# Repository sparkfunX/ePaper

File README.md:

SparkFun 3 Color ePaper Displays
===========================================================

[*SparkX 3 Color ePaper Display - 1.54" (SPX-14892)*](https://www.sparkfun.com/products/14892)

Repository Contents
-------------------

* **/1.54in display** - Datasheets and board files for the 1.54" display
* **/4.2in display** - Datasheets for the 4.2" display
* **/7.5in display** - Datasheets for the 7.5" display
* **ePaper.lbr** - Eagle library for ePaper board components

License Information
-------------------

This product is _**open source**_! 

Please use, reuse, and modify these files as you see fit. Please maintain attribution to SparkFun Electronics and release anything derivative under the same license.

Distributed as-is; no warranty is given.

- Your friends at SparkFun.

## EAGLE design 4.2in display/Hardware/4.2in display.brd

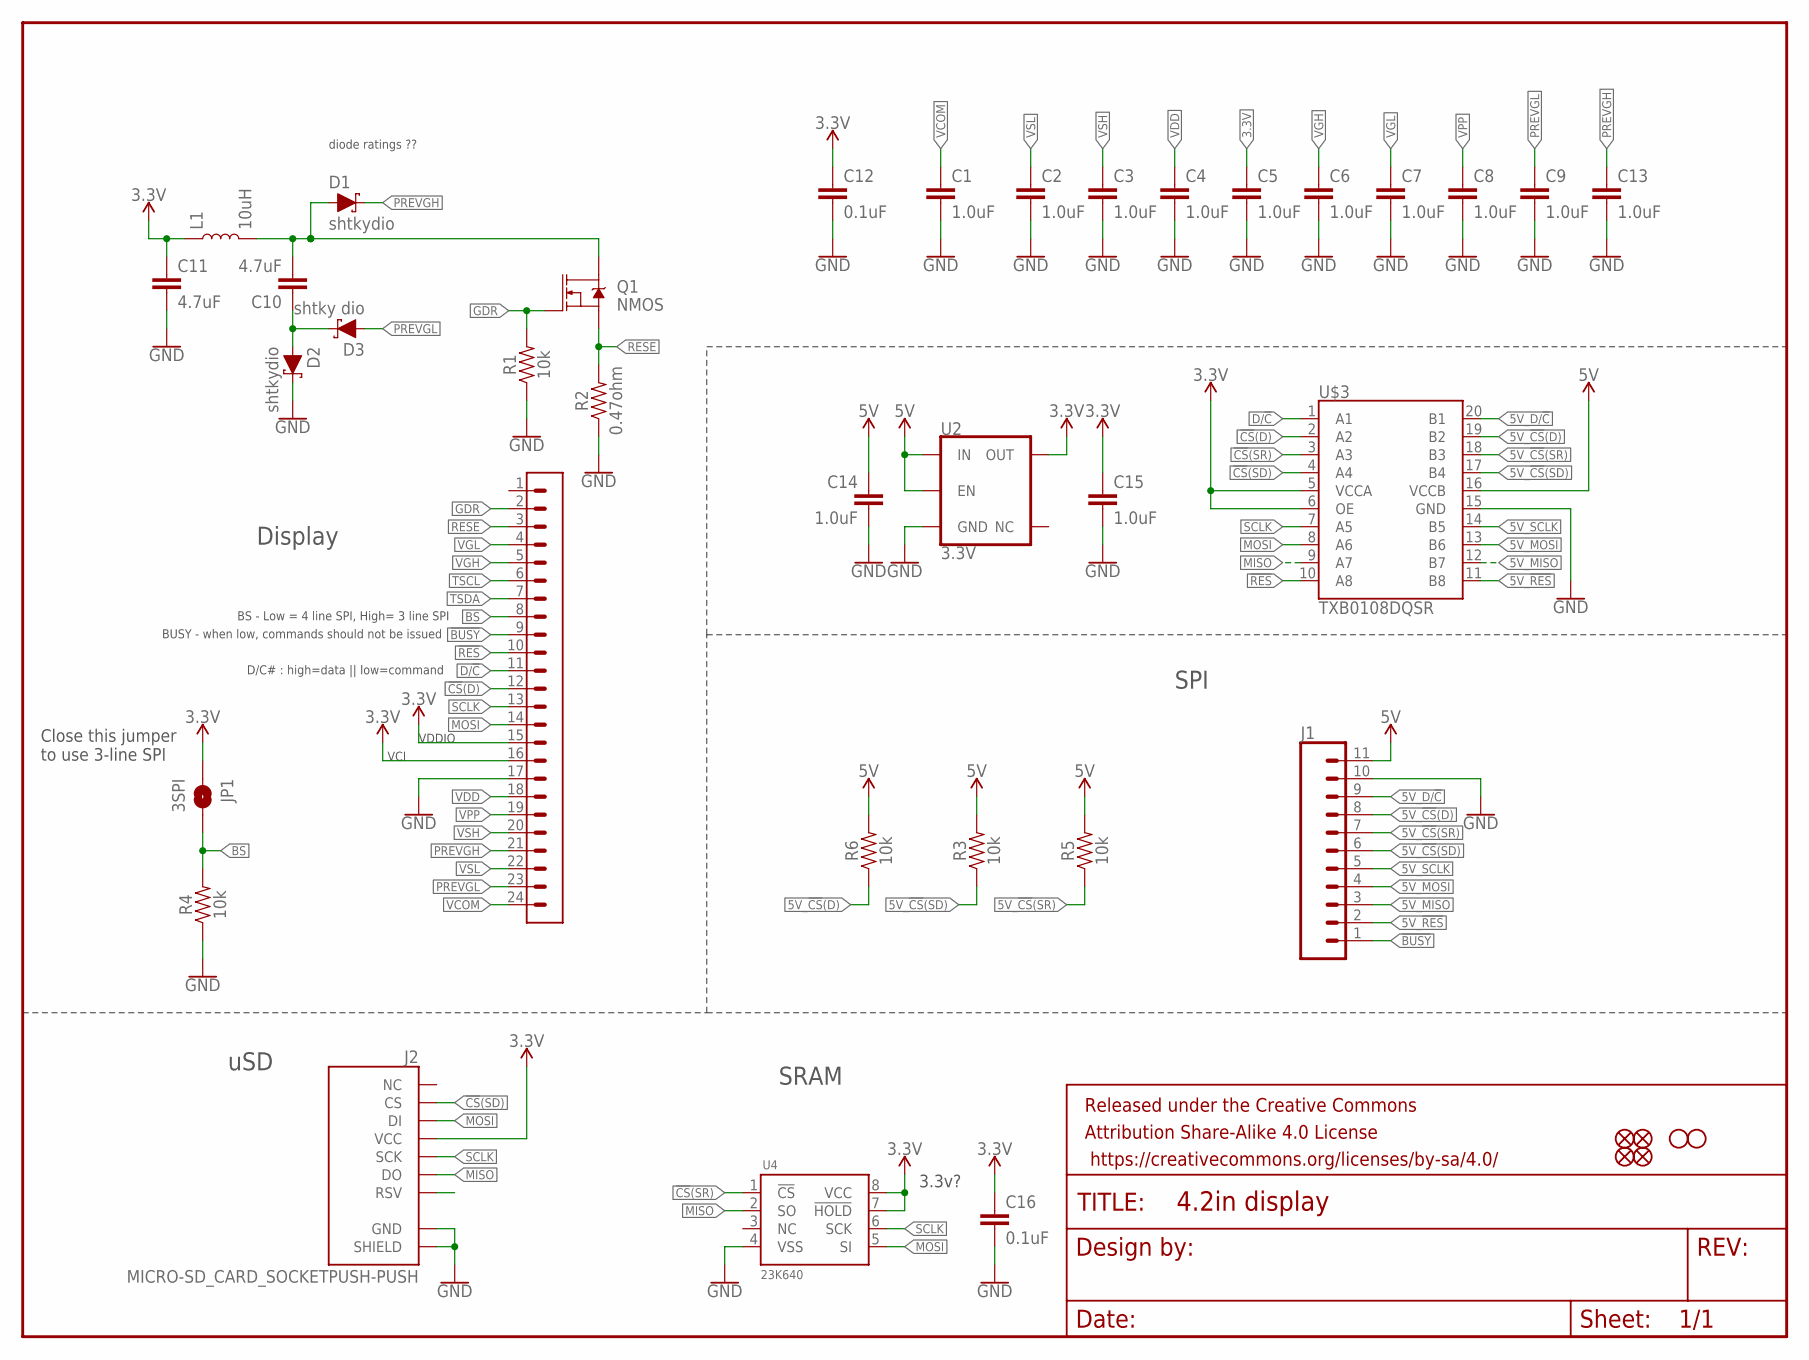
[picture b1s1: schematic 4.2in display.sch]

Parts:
C1, C14, C15: 1.0uF; 0603
C2, C3, C4, C5, C6, C7, C8, C9, C13: 1.0uF; 0805
C10, C11: 4.7uF; 0805
C12, C16: 0.1uF; 0603
D1, D2: shtkydio; SOD-323
D3: shtky dio; SOD-323
FD1, FD2, FD3, FD4: FIDUCIALUFIDUCIAL; FIDUCIAL-MICRO
FRAME1: FRAME-LETTER; CREATIVE_COMMONS
H1, H2: STAND-OFF
J1: CONN_111X11_NO_SILK; 1X11_NO_SILK
J2: MICRO-SD_CARD_SOCKETPUSH-PUSH; MICRO-SD-SOCKET
JP1: 3SPI; SMT-JUMPER_2_NO_SILK
L1: 10uH; INDUCTOR_4.7UH
Q1: NMOS; SOT323
R1, R3, R4, R5, R6: 10k; 0603
R2: 0.47ohm; 0603
U2: 3.3V; SOT23-5
U4: 23K640; SO08
U$1: 24_PIN_FPC_0.5MM
U$3: TXB0108DQSR; UFDFN-20

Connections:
3.3V: C5.1, C11.1, C12.1, C15.1, C16.1, J2.VCC, JP1.1, L1.P$1 (1), U2.5 (OUT), U4.7 (!HOLD), U4.8 (VCC), U$1.15, U$1.16, U$3.5 (VCCA), U$3.6 (OE)
5V: C14.1, J1.11, R3.2, R5.2, R6.2, U2.1 (IN), U2.3 (EN), U$3.16 (VCCB)
5V_!CS!(D): J1.8, R6.1, U$3.19 (B2)
5V_!CS!(SD): J1.6, R3.1, U$3.17 (B4)
5V_!CS!(SR): J1.7, R5.1, U$3.18 (B3)
5V_!RES: J1.2, U$3.11 (B8)
5V_D/!C: J1.9, U$3.20 (B1)
5V_MISO: J1.3, U$3.12 (B7)
5V_MOSI: J1.4, U$3.13 (B6)
5V_SCLK: J1.5, U$3.14 (B5)
!BUSY: J1.1, U$1.9
!CS!(D): U$1.12, U$3.2 (A2)
!CS!(SD): J2.CS, U$3.4 (A4)
!CS!(SR): U4.1 (!CS), U$3.3 (A3)
!RES: U$1.10, U$3.10 (A8)
BS: JP1.2, R4.2, U$1.8
D/!C: U$1.11, U$3.1 (A1)
GDR: Q1.1 (G), R1.2, U$1.2
GND: C1.2, C2.2, C3.2, C4.2, C5.2, C6.2, C7.2, C8.2, C9.2, C11.2, C12.2, C13.2, C14.2, C15.2, C16.2, D2.C, J1.10, J2.CD1 (SHIELD), J2.GND, R1.1, R2.1, R4.1, U2.2 (GND), U4.4 (VSS), U$1.17, U$3.15 (GND)
MISO: J2.DO, U4.2 (SO), U$3.9 (A7)
MOSI: J2.DI, U4.5 (SI), U$1.14, U$3.8 (A6)
unnamed: C10.1, D2.A, D3.C
unnamed: C10.2, D1.A, L1.P$2 (2), Q1.3 (D)
PREVGH: C13.1, D1.C, U$1.21
PREVGL: C9.1, D3.A, U$1.23
RESE: Q1.2 (S), R2.2, U$1.3
SCLK: J2.SCLK (SCK), U4.6 (SCK), U$1.13, U$3.7 (A5)
TSCL: U$1.6
TSDA: U$1.7
VCOM: C1.1, U$1.24
VDD: C4.1, U$1.18
VGH: C6.1, U$1.5
VGL: C7.1, U$1.4
VPP: C8.1, U$1.19
VSH: C3.1, U$1.20
VSL: C2.1, U$1.22

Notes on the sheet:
D/C# : high=data || low=command
BUSY - when low, commands should not be issued
BS - Low = 4 line SPI, High= 3 line SPI
diode ratings ??
VDDIO
VCI
Display
SPI
uSD
3.3v?
Close this jumper to use 3-line SPI
SRAM

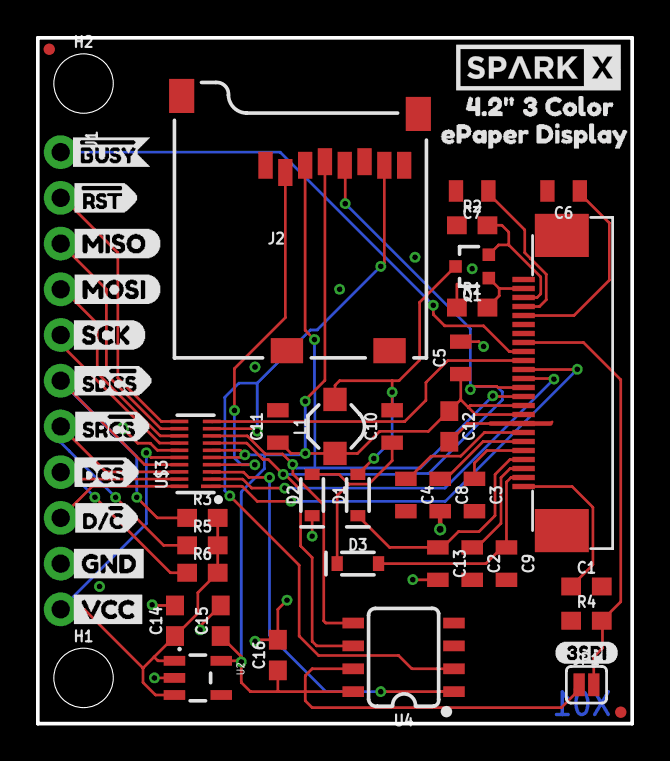
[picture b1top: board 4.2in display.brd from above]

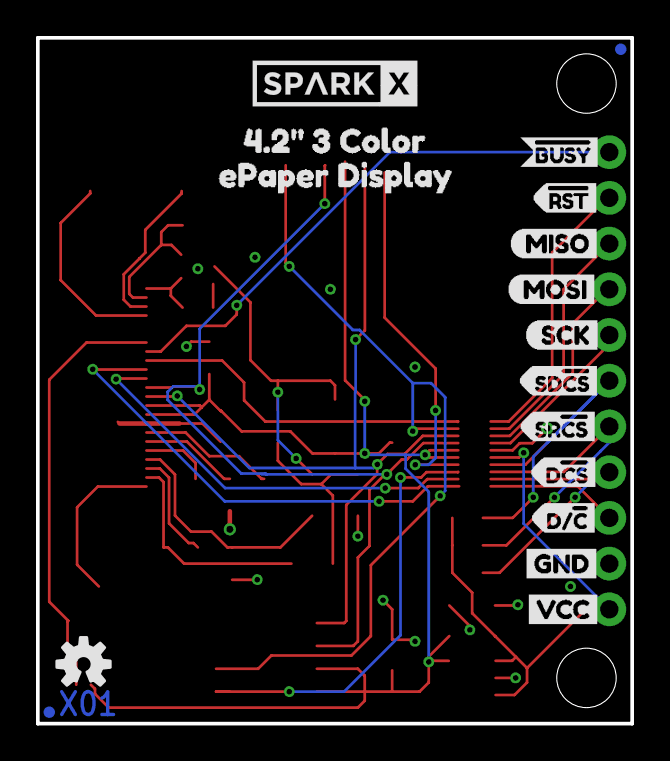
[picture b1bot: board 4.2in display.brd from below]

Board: 2 copper layers, 33.0 x 38.1 mm, 73 parts (18 on the bottom side), 34 nets.

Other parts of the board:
U$2: OSHW-LOGO-S
U$4: #BUSY0
U$5, U$18: SPARKX-LOGO4; SPARKX-MEDIUM
U$6: #BUSY1
U$7: D##C10
U$8: MISO1
U$9: D#CS2
U$10: SD#CS0
U$11: #RST1
U$12: 3SPI0
U$13, U$21: VCC9
U$14: GND9
U$15: SR#CS1
U$16: MOSI0
U$17: SCK2
U$19: 3_COLOR2
U$20: #RST2
U$22: 3_COLOR3
U$23: 4#2#0
U$24: MISO3
U$25: MOSI4
U$26: SCK5
U$27: SD#CS6
U$28: SR#CS7
U$29: D#CS8
U$30: D##C9
U$31: GND11
U$32: EPAPER_DISPLAY5
U$33: EPAPER_DISPLAY4
U$34: 4#2#1

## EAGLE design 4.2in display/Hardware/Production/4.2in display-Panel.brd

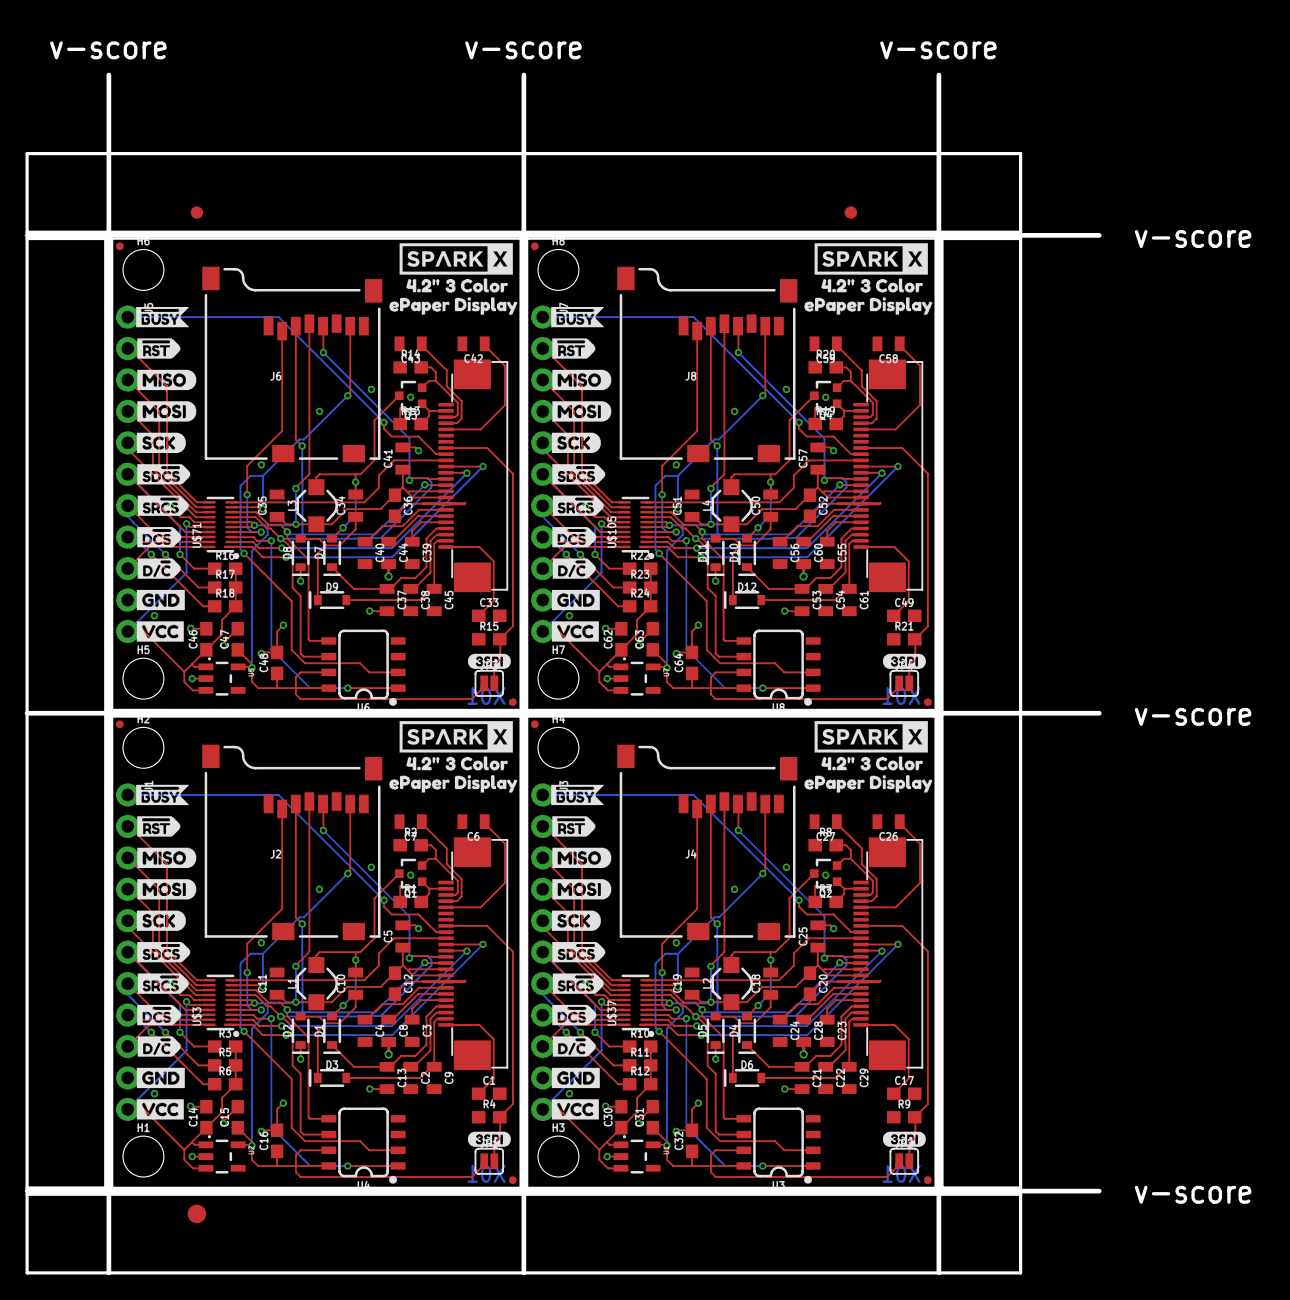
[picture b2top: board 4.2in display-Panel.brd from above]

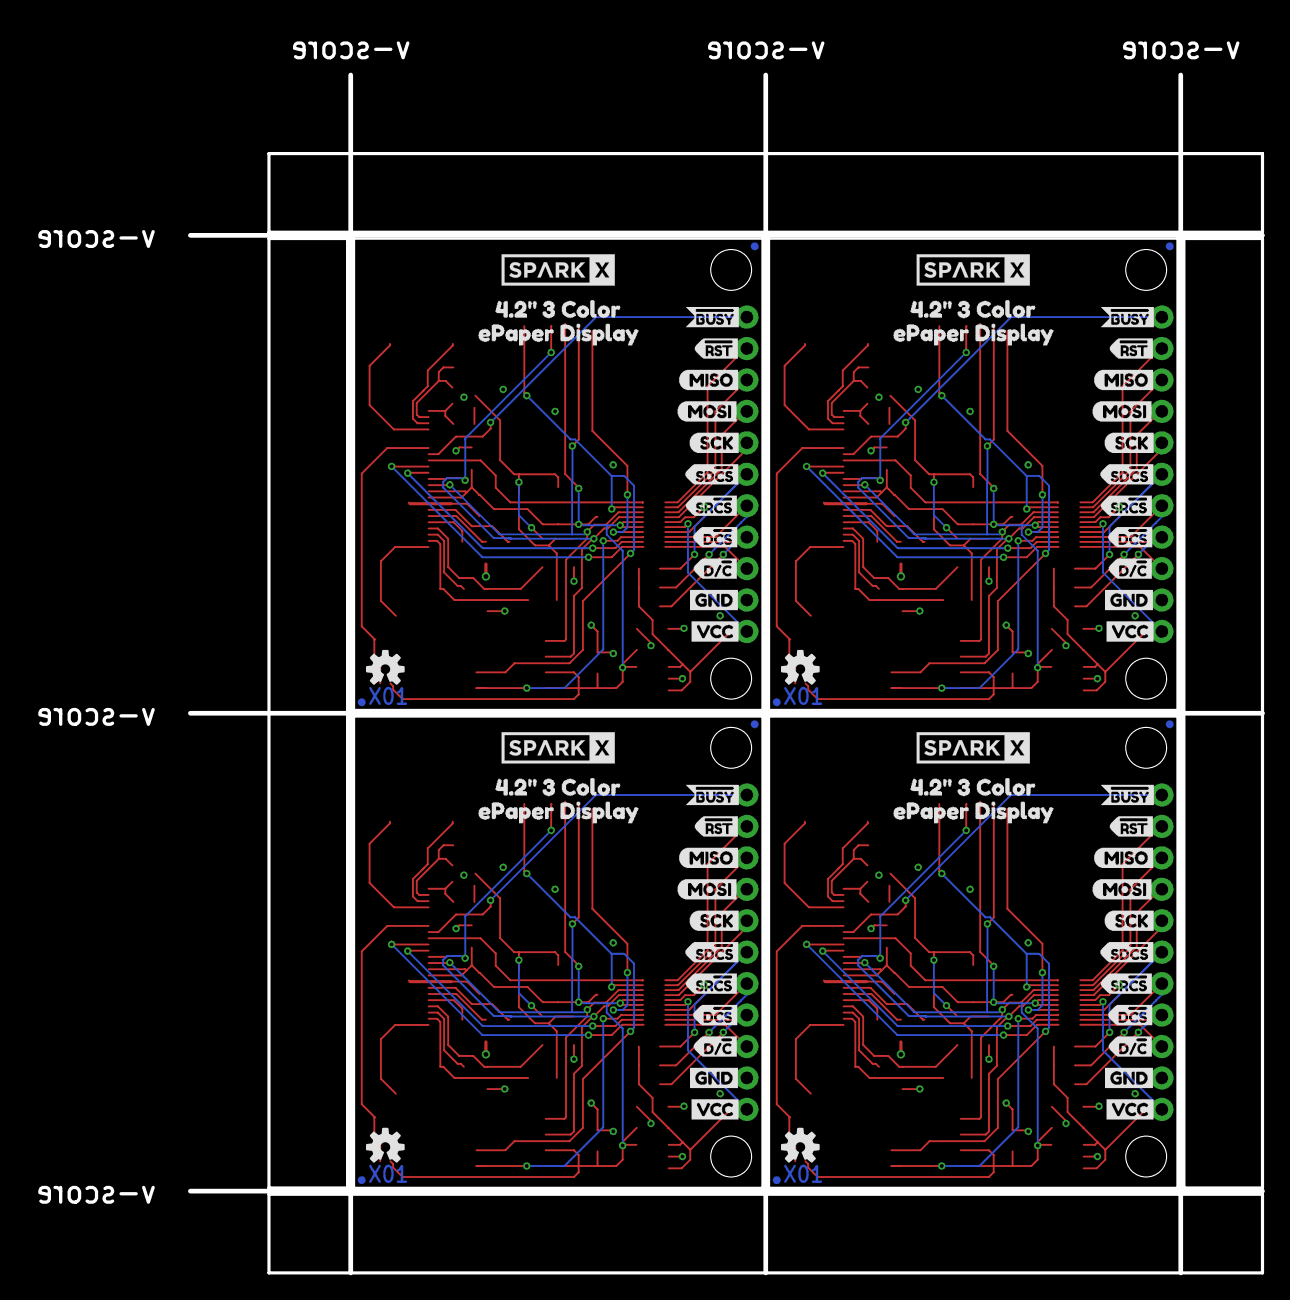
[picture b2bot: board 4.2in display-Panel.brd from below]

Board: 2 copper layers, 99.8 x 100.6 mm, 291 parts (72 on the bottom side), 136 nets.

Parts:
C1, C14, C15, C17, C30, C31, C33, C46, C47, C49, C62, C63: 1.0uF; 0603
C2, C3, C4, C5, C6, C7, C8, C9, C13, C21, C22, C23, C24, C25, C26, C27, C28, C29, C37, C38, C39, C40, C41, C42, C43, C44, C45, C53, C54, C55, C56, C57, C58, C59, C60, C61: 1.0uF; 0805
C10, C11, C18, C19, C34, C35, C50, C51: 4.7uF; 0805
C12, C16, C20, C32, C36, C48, C52, C64: 0.1uF; 0603
D1, D2, D3, D4, D5, D6, D7, D8, D9, D10, D11, D12: 0.5A/40V/420mV; SOD-323
E$1, E$2: FIDUCIAL-1X2
E$3: FIDUCIAL-1.5X3
FD1, FD2, FD3, FD4, FD5, FD6, FD7, FD8, FD9, FD10, FD11, FD12, FD13, FD14, FD15, FD16: FIDUCIALUFIDUCIAL; FIDUCIAL-MICRO
H1, H2, H3, H4, H5, H6, H7, H8: STAND-OFF
J1, J3, J5, J7: 1X11_NO_SILK
J2, J4, J6, J8: MICRO-SD_CARD_SOCKETPUSH-PUSH; MICRO-SD-SOCKET
JP1, JP2, JP3, JP4: 3SPI; SMT-JUMPER_2_NO_SILK
L1, L2, L3, L4: 10uH; INDUCTOR_4.7UH
Q1, Q2, Q3, Q4: 310mA/60V/1.6Ω; SOT323
R1, R3, R4, R5, R6, R7, R9, R10, R11, R12, R13, R15, R16, R17, R18, R19, R21, R22, R23, R24: 10k; 0603
R2, R8, R14, R20: 0.47ohm; 0603
U1, U2, U5, U7: 3.3V; SOT23-5
U3, U4, U6, U8: 23K640; SO08
U$1, U$35, U$69, U$103: 24_PIN_FPC_0.5MM
U$2, U$36, U$70, U$104: OSHW-LOGO-S
U$3, U$37, U$71, U$105: TXB0108DQSR; UFDFN-20
U$4, U$47, U$81, U$115: #BUSY0
U$5, U$18, U$48, U$62, U$82, U$96, U$116, U$130: SPARKX-LOGO4; SPARKX-MEDIUM
U$6, U$49, U$83, U$117: #BUSY1
U$7, U$38, U$72, U$106: D##C10
U$8, U$44, U$78, U$112: MISO1
U$9, U$41, U$75, U$109: D#CS2
U$10, U$42, U$76, U$110: SD#CS0
U$11, U$39, U$73, U$107: #RST1
U$12, U$59, U$93, U$127: 3SPI0
U$13, U$21, U$60, U$61, U$94, U$95, U$128, U$129: VCC9
U$14, U$40, U$74, U$108: GND9
U$15, U$43, U$77, U$111: SR#CS1
U$16, U$45, U$79, U$113: MOSI0
U$17, U$46, U$80, U$114: SCK2
U$19, U$63, U$97, U$131: 3_COLOR2
U$20, U$50, U$84, U$118: #RST2
U$22, U$64, U$98, U$132: 3_COLOR3
U$23, U$65, U$99, U$133: 4#2#0
U$24, U$51, U$85, U$119: MISO3
U$25, U$52, U$86, U$120: MOSI4
U$26, U$53, U$87, U$121: SCK5
U$27, U$54, U$88, U$122: SD#CS6
U$28, U$55, U$89, U$123: SR#CS7
U$29, U$56, U$90, U$124: D#CS8
U$30, U$57, U$91, U$125: D##C9
U$31, U$58, U$92, U$126: GND11
U$32, U$67, U$101, U$135: EPAPER_DISPLAY5
U$33, U$66, U$100, U$134: EPAPER_DISPLAY4
U$34, U$68, U$102, U$136: 4#2#1

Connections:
3.3V: C5.1, C11.1, C12.1, C15.1, C16.1, J2.VCC, JP1.1, L1.P$1, U2.5, U4.7, U4.8, U$1.15, U$1.16, U$3.5, U$3.6
3.3V1: C19.1, C20.1, C25.1, C31.1, C32.1, J4.VCC, JP2.1, L2.P$1, U1.5, U3.7, U3.8, U$35.15, U$35.16, U$37.5, U$37.6
3.3V2: C35.1, C36.1, C41.1, C47.1, C48.1, J6.VCC, JP3.1, L3.P$1, U5.5, U6.7, U6.8, U$69.15, U$69.16, U$71.5, U$71.6
3.3V3: C51.1, C52.1, C57.1, C63.1, C64.1, J8.VCC, JP4.1, L4.P$1, U7.5, U8.7, U8.8, U$103.15, U$103.16, U$105.5, U$105.6
5V: C14.1, J1.11, R3.2, R5.2, R6.2, U2.1, U2.3, U$3.16
5V1: C30.1, J3.11, R10.2, R11.2, R12.2, U1.1, U1.3, U$37.16
5V2: C46.1, J5.11, R16.2, R17.2, R18.2, U5.1, U5.3, U$71.16
5V3: C62.1, J7.11, R22.2, R23.2, R24.2, U7.1, U7.3, U$105.16
5V_!CS!(D): J1.8, R6.1, U$3.19
5V_!CS!(D)1: J3.8, R12.1, U$37.19
5V_!CS!(D)2: J5.8, R18.1, U$71.19
5V_!CS!(D)3: J7.8, R24.1, U$105.19
5V_!CS!(SD): J1.6, R3.1, U$3.17
5V_!CS!(SD)1: J3.6, R10.1, U$37.17
5V_!CS!(SD)2: J5.6, R16.1, U$71.17
5V_!CS!(SD)3: J7.6, R22.1, U$105.17
5V_!CS!(SR): J1.7, R5.1, U$3.18
5V_!CS!(SR)1: J3.7, R11.1, U$37.18
5V_!CS!(SR)2: J5.7, R17.1, U$71.18
5V_!CS!(SR)3: J7.7, R23.1, U$105.18
5V_!RES: J1.2, U$3.11
5V_!RES1: J3.2, U$37.11
5V_!RES2: J5.2, U$71.11
5V_!RES3: J7.2, U$105.11
5V_D/!C: J1.9, U$3.20
5V_D/!C1: J3.9, U$37.20
5V_D/!C2: J5.9, U$71.20
5V_D/!C3: J7.9, U$105.20
5V_MISO: J1.3, U$3.12
5V_MISO1: J3.3, U$37.12
5V_MISO2: J5.3, U$71.12
5V_MISO3: J7.3, U$105.12
5V_MOSI: J1.4, U$3.13
5V_MOSI1: J3.4, U$37.13
5V_MOSI2: J5.4, U$71.13
5V_MOSI3: J7.4, U$105.13
5V_SCLK: J1.5, U$3.14
5V_SCLK1: J3.5, U$37.14
5V_SCLK2: J5.5, U$71.14
5V_SCLK3: J7.5, U$105.14
!BUSY: J1.1, U$1.9
!BUSY1: J3.1, U$35.9
!BUSY2: J5.1, U$69.9
!BUSY3: J7.1, U$103.9
!CS!(D): U$1.12, U$3.2
!CS!(D)1: U$35.12, U$37.2
!CS!(D)2: U$69.12, U$71.2
!CS!(D)3: U$103.12, U$105.2
!CS!(SD): J2.CS, U$3.4
!CS!(SD)1: J4.CS, U$37.4
!CS!(SD)2: J6.CS, U$71.4
!CS!(SD)3: J8.CS, U$105.4
!CS!(SR): U4.1, U$3.3
!CS!(SR)1: U3.1, U$37.3
!CS!(SR)2: U6.1, U$71.3
!CS!(SR)3: U8.1, U$105.3
!RES: U$1.10, U$3.10
!RES1: U$35.10, U$37.10
!RES2: U$69.10, U$71.10
!RES3: U$103.10, U$105.10
BS: JP1.2, R4.2, U$1.8
BS1: JP2.2, R9.2, U$35.8
BS2: JP3.2, R15.2, U$69.8
BS3: JP4.2, R21.2, U$103.8
D/!C: U$1.11, U$3.1
D/!C1: U$35.11, U$37.1
D/!C2: U$69.11, U$71.1
D/!C3: U$103.11, U$105.1
GDR: Q1.1, R1.2, U$1.2
GDR1: Q2.1, R7.2, U$35.2
GDR2: Q3.1, R13.2, U$69.2
GDR3: Q4.1, R19.2, U$103.2
GND: C1.2, C2.2, C3.2, C4.2, C5.2, C6.2, C7.2, C8.2, C9.2, C11.2, C12.2, C13.2, C14.2, C15.2, C16.2, D2.C, J1.10, J2.CD1, J2.GND, R1.1, R2.1, R4.1, U2.2, U4.4, U$1.17, U$3.15
GND1: C17.2, C19.2, C20.2, C21.2, C22.2, C23.2, C24.2, C25.2, C26.2, C27.2, C28.2, C29.2, C30.2, C31.2, C32.2, D5.C, J3.10, J4.CD1, J4.GND, R7.1, R8.1, R9.1, U1.2, U3.4, U$35.17, U$37.15
GND2: C33.2, C35.2, C36.2, C37.2, C38.2, C39.2, C40.2, C41.2, C42.2, C43.2, C44.2, C45.2, C46.2, C47.2, C48.2, D8.C, J5.10, J6.CD1, J6.GND, R13.1, R14.1, R15.1, U5.2, U6.4, U$69.17, U$71.15
GND3: C49.2, C51.2, C52.2, C53.2, C54.2, C55.2, C56.2, C57.2, C58.2, C59.2, C60.2, C61.2, C62.2, C63.2, C64.2, D11.C, J7.10, J8.CD1, J8.GND, R19.1, R20.1, R21.1, U7.2, U8.4, U$103.17, U$105.15
MISO: J2.DO, U4.2, U$3.9
MISO1: J4.DO, U3.2, U$37.9
MISO2: J6.DO, U6.2, U$71.9
MISO3: J8.DO, U8.2, U$105.9
MOSI: J2.DI, U4.5, U$1.14, U$3.8
MOSI1: J4.DI, U3.5, U$35.14, U$37.8
MOSI2: J6.DI, U6.5, U$69.14, U$71.8
MOSI3: J8.DI, U8.5, U$103.14, U$105.8
unnamed: C18.1, D5.A, D6.C
unnamed: C10.1, D2.A, D3.C
unnamed: C18.2, D4.A, L2.P$2, Q2.3
unnamed: C10.2, D1.A, L1.P$2, Q1.3
unnamed: C34.1, D8.A, D9.C
unnamed: C34.2, D7.A, L3.P$2, Q3.3
unnamed: C50.1, D11.A, D12.C
unnamed: C50.2, D10.A, L4.P$2, Q4.3
PREVGH: C13.1, D1.C, U$1.21
PREVGH1: C21.1, D4.C, U$35.21
PREVGH2: C37.1, D7.C, U$69.21
PREVGH3: C53.1, D10.C, U$103.21
PREVGL: C9.1, D3.A, U$1.23
PREVGL1: C29.1, D6.A, U$35.23
PREVGL2: C45.1, D9.A, U$69.23
PREVGL3: C61.1, D12.A, U$103.23
RESE: Q1.2, R2.2, U$1.3
RESE1: Q2.2, R8.2, U$35.3
RESE2: Q3.2, R14.2, U$69.3
RESE3: Q4.2, R20.2, U$103.3
SCLK: J2.SCLK, U4.6, U$1.13, U$3.7
SCLK1: J4.SCLK, U3.6, U$35.13, U$37.7
SCLK2: J6.SCLK, U6.6, U$69.13, U$71.7
SCLK3: J8.SCLK, U8.6, U$103.13, U$105.7
VCOM: C1.1, U$1.24
VCOM1: C17.1, U$35.24
VCOM2: C33.1, U$69.24
VCOM3: C49.1, U$103.24
VDD: C4.1, U$1.18
VDD1: C24.1, U$35.18
VDD2: C40.1, U$69.18
VDD3: C56.1, U$103.18
VGH: C6.1, U$1.5
VGH1: C26.1, U$35.5
VGH2: C42.1, U$69.5
VGH3: C58.1, U$103.5
VGL: C7.1, U$1.4
VGL1: C27.1, U$35.4
VGL2: C43.1, U$69.4
VGL3: C59.1, U$103.4
VPP: C8.1, U$1.19
VPP1: C28.1, U$35.19
VPP2: C44.1, U$69.19
VPP3: C60.1, U$103.19
VSH: C3.1, U$1.20
VSH1: C23.1, U$35.20
VSH2: C39.1, U$69.20
VSH3: C55.1, U$103.20
VSL: C2.1, U$1.22
VSL1: C22.1, U$35.22
VSL2: C38.1, U$69.22
VSL3: C54.1, U$103.22

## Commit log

2018-08-15 add datasheets
2018-08-15 documentation
2018-08-22 minor rev
2018-08-22 added boards
2018-09-18 brds
2018-09-18 rmv old
2018-09-25 Revert "asm"
    This reverts commit 79dfb80ccaf4c70f6c8d653a0d6d0867a03f4c3a.
2018-10-09 Revert "Revert "asm""
    This reverts commit b489ea2ff6e59cc2c3bae19cf3fe86e4ee51237d.
2018-10-09 Revert "Revert "Revert "asm"""
    This reverts commit 13aa5e244575f702f785403d246ecc40f8071a55.
2018-10-09 Revert "sch"
    This reverts commit 65ffcdcff918ffc3cbfeebb47afa4d674ba5142f.
2018-10-09 4.2 schematic update

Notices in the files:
parts and their libraries:
SparkFun-Aesthetics: Licensing: Creative Commons ShareAlike 4.0 International - https://creativecommons.org/licenses/by-sa/4.0
SparkFun-Aesthetics: Released under the Creative Commons Attribution Share-Alike 4.0 License
SparkFun-Aesthetics: https://creativecommons.org/licenses/by-sa/4.0
